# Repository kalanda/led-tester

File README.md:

# Led tester

Device for testing brightness and current consumption of through-hole and SMD LEDs. 

## Mission

With this device you can test any bipolar LEDs and see with your eyes the real brightness and current consumption using a specific resistor value and logic voltage. That's useful because the brightness is different for each color and type of led and this device will help you to choose the right values for your project in a real environment instead of reading the datasheet.

## Features

- Powered with just 4xAA batteries or 6v-12v
- Selector for 5v and 3.3v logic with included voltage regulators
- Terminal connector for multimeter current testing (you need to short this terminals when is not used)
- Valid for SMD and through-hole leds
- Printed silkscreen table with calculated values for each resistor, supply voltage and 'Vf' of the LED
- Selector of current limiting resistor with most common values from 30Ω to 10KΩ

## Schema and board

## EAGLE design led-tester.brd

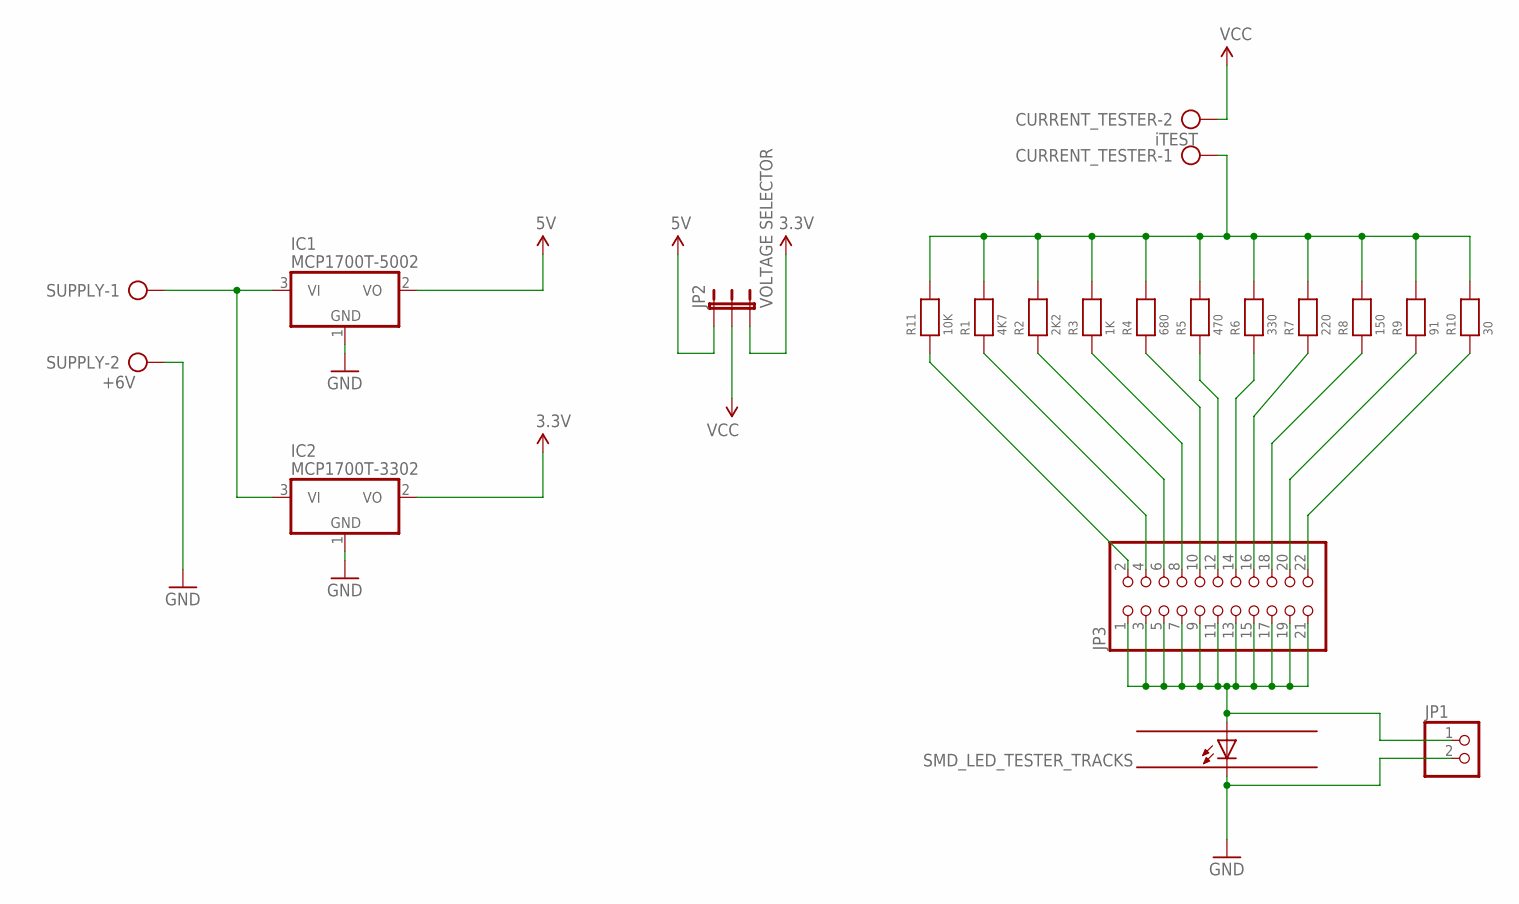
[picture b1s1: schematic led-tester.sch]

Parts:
CURRENT_TESTER: iTEST; TERMINAL_BLOCK_X2
IC1: MCP1700T-5002; SOT23
IC2: MCP1700T-3302; SOT23
JP1: PINHD-1X2; 1X02
JP2: VOLTAGE SELECTOR; 1X03
JP3: PINHD-2X11; 2X11
R1: 4K7; 0805
R2: 2K2; 0805
R3: 1K; 0805
R4: 680; 0805
R5: 470; 0805
R6: 330; 0805
R7: 220; 0805
R8: 150; 0805
R9: 91; 0805
R10: 30; 0805
R11: 10K; 0805
SUPPLY: +6V; TERMINAL_BLOCK_X2
U$1: SMD_LED_TESTER_TRACKS

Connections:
3.3V: IC2.2 (VO), JP2.3
5V: IC1.2 (VO), JP2.1
GND: IC1.1 (GND), IC2.1 (GND), JP1.2, SUPPLY.2, U$1.P$2 (C)
unnamed: JP3.22, R10.1
unnamed: JP3.20, R9.1
unnamed: JP3.18, R8.1
unnamed: JP3.16, R7.1
unnamed: JP3.14, R6.1
unnamed: JP3.12, R5.1
unnamed: JP3.10, R4.1
unnamed: JP3.8, R3.1
unnamed: JP3.6, R2.1
unnamed: JP3.4, R1.1
unnamed: JP1.1, JP3.1, JP3.3, JP3.5, JP3.7, JP3.9, JP3.11, JP3.13, JP3.15, JP3.17, JP3.19, JP3.21, U$1.P$1 (A)
unnamed: JP3.2, R11.1
unnamed: CURRENT_TESTER.1, R1.2, R2.2, R3.2, R4.2, R5.2, R6.2, R7.2, R8.2, R9.2, R10.2, R11.2
unnamed: IC1.3 (VI), IC2.3 (VI), SUPPLY.1
VCC: CURRENT_TESTER.2, JP2.2

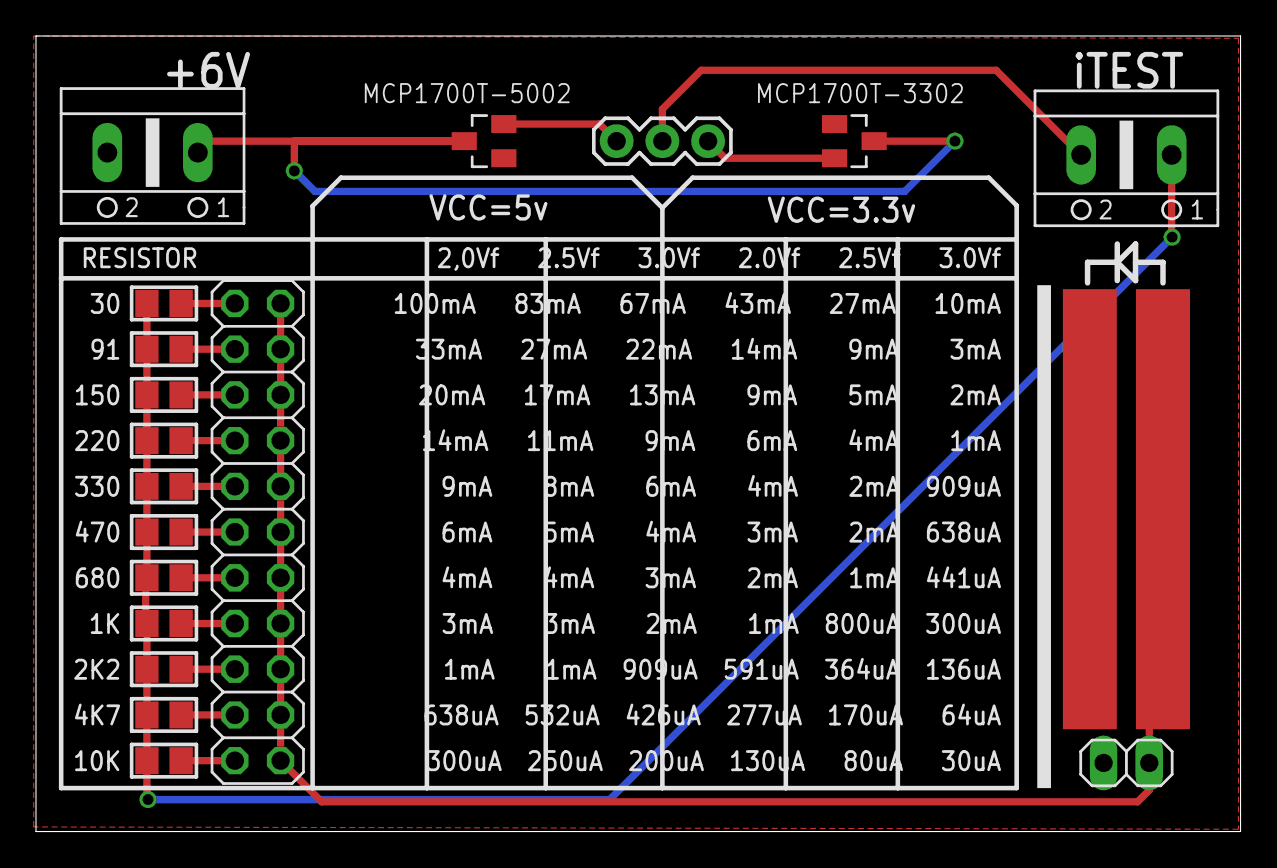
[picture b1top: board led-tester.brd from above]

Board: 2 copper layers, 66.9 x 44.2 mm, 19 parts (0 on the bottom side), 18 nets.

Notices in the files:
parts and their libraries:
SparkFun-Passives: Licensing: CC v3.0 Share-Alike You are welcome to use this library for commercial purposes.
microbuilder: This work is placed in the public domain, and may be freely used for commercial and non-commercial work with the following conditions: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
